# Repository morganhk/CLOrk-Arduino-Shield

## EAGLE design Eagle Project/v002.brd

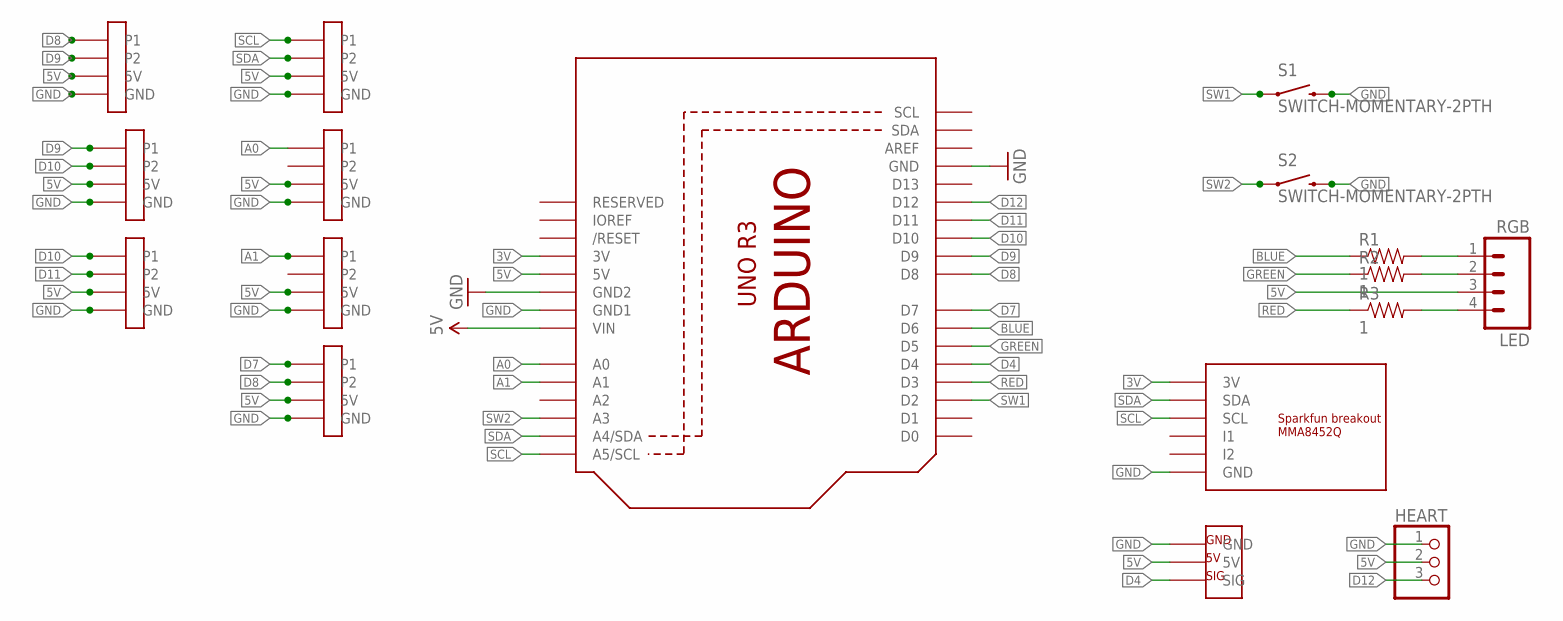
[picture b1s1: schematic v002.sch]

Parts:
HEART: PINHD-1X3CB; 1X03-CLEANBIG
LED: RGB; 1X04
R1, R2, R3: 1; AXIAL-0.4
S1, S2: SWITCH-MOMENTARY-2PTH; TACTILE-PTH
U1: ARDUINOR3-BPLACE
U$1: MMA8452Q; SPARKFUN-MMA8452Q
U$2: PING)))
U$4, U$5, U$6, U$7, U$8, U$9, U$10: 4PINJST

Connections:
3V: U1.3V, U$1.3V
5V: HEART.2, LED.3, U1.5V, U1.VIN, U$2.5V, U$4.5V, U$5.5V, U$6.5V, U$7.5V, U$8.5V, U$9.5V, U$10.5V
A0: U1.A0, U$5.P1
A1: U1.A1, U$6.P1
BLUE: R1.P$1 (1), U1.D6
D4: U1.D4, U$2.SIG
D7: U1.D7, U$7.P1
D8: U1.D8, U$7.P2, U$8.P1
D9: U1.D9, U$8.P2, U$9.P1
D10: U1.D10, U$9.P2, U$10.P1
D11: U1.D11, U$10.P2
D12: HEART.3, U1.D12
GND: HEART.1, S1.3 (2), S2.3 (2), U1.GND, U1.GND1, U1.GND2, U$1.GND, U$2.GND, U$4.GND, U$5.GND, U$6.GND, U$7.GND, U$8.GND, U$9.GND, U$10.GND
GREEN: R2.P$1 (1), U1.D5
unnamed: LED.1, R1.P$2 (2)
unnamed: LED.2, R2.P$2 (2)
unnamed: LED.4, R3.P$2 (2)
RED: R3.P$1 (1), U1.D3
SCL: U1.A5 (A5/SCL), U$1.SCL, U$4.P1
SDA: U1.A4 (A4/SDA), U$1.SDA, U$4.P2
SW1: S1.1, U1.D2
SW2: S2.1, U1.A3

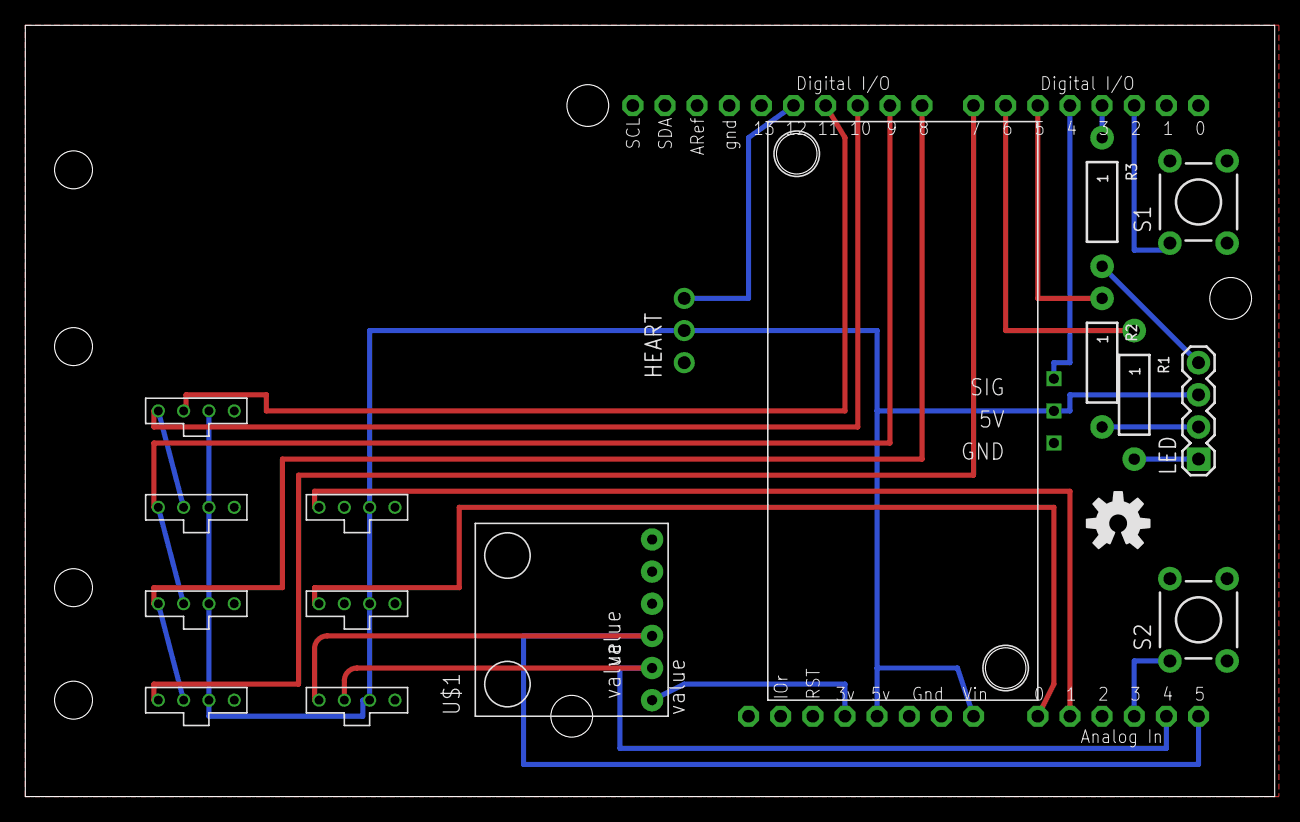
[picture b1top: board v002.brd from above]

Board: 4 copper layers, 98.7 x 61.0 mm, 18 parts (0 on the bottom side), 22 nets.

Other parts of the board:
U$3: OSHW-LOGO-M

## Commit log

2013-11-07 GitIgnoring first
    Setting up the ignore list.
    Based on
    https://github.com/github/gitignore/blob/master/Eagle.gitignore and
    https://help.github.com/articles/ignoring-files
2013-11-07 First committ after submission to PCB manufacturer
2013-11-15 Arduino sample code and V002
2013-11-28 updated for 3 sensors

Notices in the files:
parts and their libraries:
SparkFun-Electromechanical: Licensing: CC v3.0 Share-Alike You are welcome to use this library for commercial purposes.
